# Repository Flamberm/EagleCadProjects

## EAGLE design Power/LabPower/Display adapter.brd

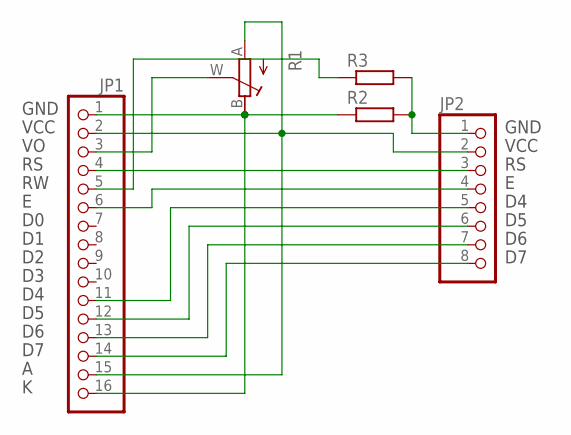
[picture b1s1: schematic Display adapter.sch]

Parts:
JP1: PINHD-1X16; 1X16
JP2: PINHD-1X8; 1X08
R1: R_POTTURN-X; RJ9W
R2, R3: R_1206; R1206

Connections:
unnamed: JP1.5, R3.1
unnamed: JP2.1, R2.2, R3.2
unnamed: JP1.11, JP2.5
unnamed: JP1.6, JP2.4
unnamed: JP1.4, JP2.3
unnamed: JP1.1, JP1.16, R1.B (E), R2.1
unnamed: JP1.2, JP1.15, JP2.2, R1.A
unnamed: JP1.3, R1.W (S)
unnamed: JP1.12, JP2.6
unnamed: JP1.13, JP2.7
unnamed: JP1.14, JP2.8

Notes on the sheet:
GND
VCC

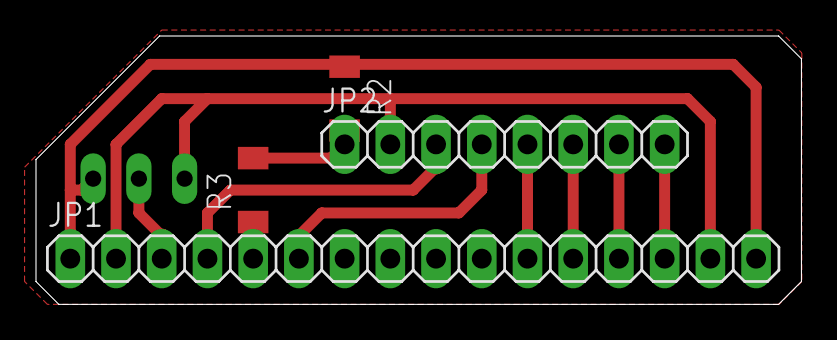
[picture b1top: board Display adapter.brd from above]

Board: 2 copper layers, 42.5 x 14.9 mm, 5 parts (1 on the bottom side), 11 nets.

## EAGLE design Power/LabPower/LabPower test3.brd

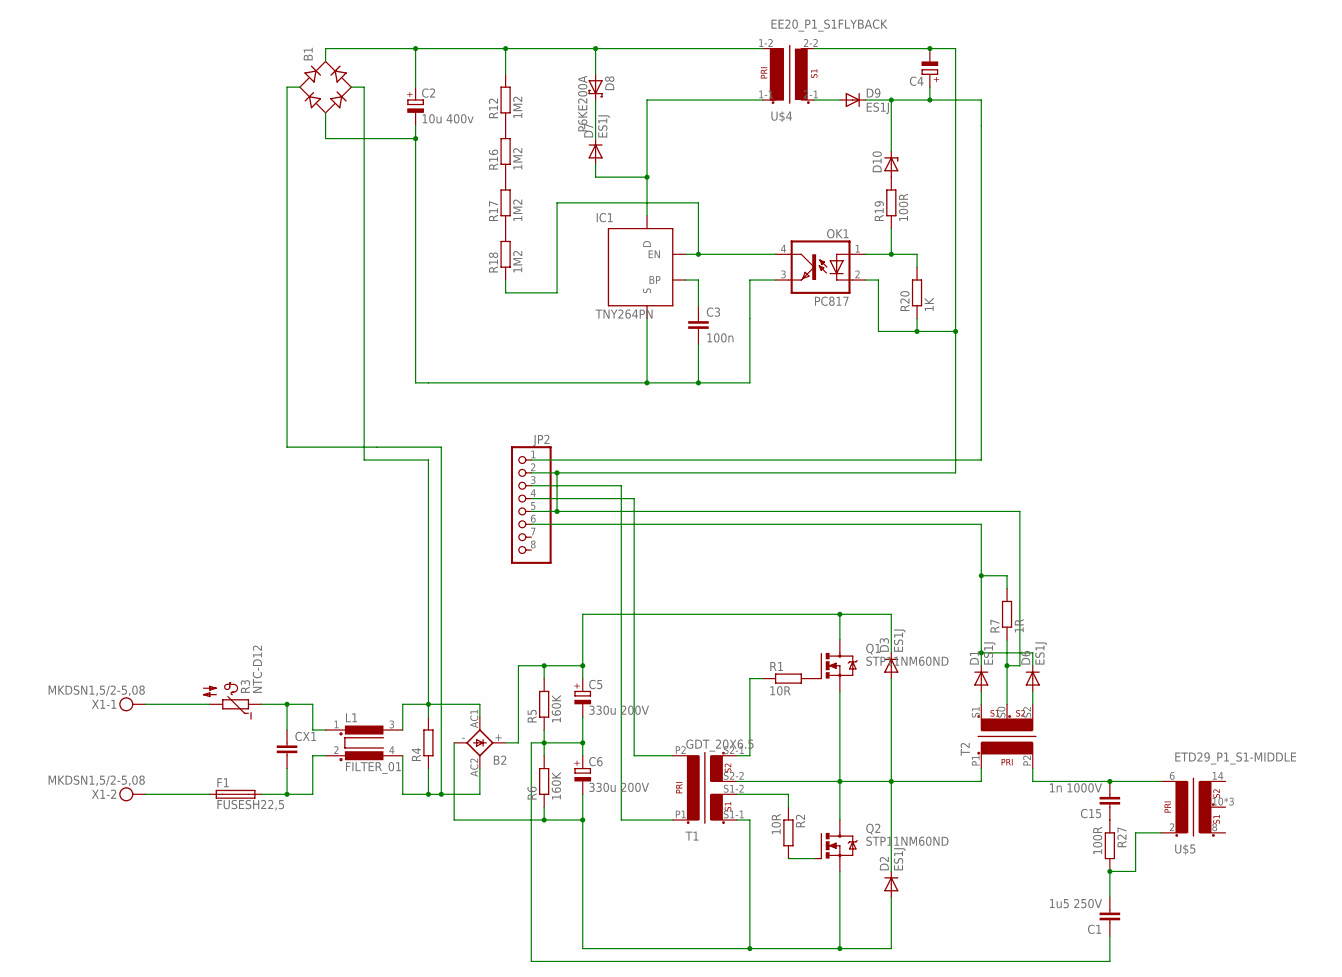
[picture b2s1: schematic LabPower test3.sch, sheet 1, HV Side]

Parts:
B1: RB1A
B2: KBL
C1: 1u5 250V; C225-074X268
C2: 10u 400v; E5-13
C3: 100n; C0805
C4: CPOL-EUE2.5-7; E2,5-7
C5, C6: 330u 200V; EB22,5D
C15: 1n 1000V; C050-025X075
CX1: CXXC15B8; XC15B8
D1, D2, D3, D6, D7, D9: ES1J; DO214AC
D8: P6KE200A; CB417-15
D10: ZENER-DIODEDO41Z10; DO41Z10
F1: FUSESH22,5; SH22,5
IC1: TNY264PN; DIP-8B
JP2: PINHD-1X8; 1X08
L1: FILTER_01; 82721K
OK1: PC817; DIL04
Q1, Q2: STP11NM60ND; TO220BV
R1, R2: 10R; R0805
R3: NTC-D12
R4: R-EU_0309/10; 0309/10
R5, R6: 160K; 0207/12
R7: 1R; R1206
R12, R16, R17, R18: 1M2; R0805
R19: 100R; R0805
R20: 1K; R0805
R27: 100R; 0617/17
T1: GDT_20X6.5
T2: CURRENT; T_10X6X3
U$4: EE20_P1_S1FLYBACK; EE20_P1_S1-REV-4PIN
U$5: ETD29_P1_S1-MIDDLE; ETD29
X1: MKDSN1,5/2-5,08

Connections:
300V: B2.+, C5.+, D3.C, Q1.D, R5.2
AC1: B1.AC1, B2.AC2 (AC1), L1.4, R4.1
AC2: B1.AC2, B2.AC1 (AC2), L1.3 (2), R4.2
unnamed: C1.1, C5.-, C6.+, R5.1, R6.2
unnamed: D2.C, D3.A, Q1.S, Q2.D, T1.S2-2, T2.P1 (P1-1)
unnamed: C1.2, R27.2, U$5.2 (P1-1)
unnamed: C15.2, T2.P2 (P1-2), U$5.6 (P1-2)
unnamed: F1.1, X1.2
unnamed: R3.2, X1.1
unnamed: CX1.1, L1.1, R3.1
unnamed: CX1.2, F1.2, L1.2 (3)
unnamed: B2.-, C6.-, D2.A, Q2.S, R6.1, T1.S1-1
unnamed: JP2.3, T1.P1 (P1-1)
unnamed: Q1.G, R1.2
unnamed: Q2.G, R2.2
unnamed: JP2.4, T1.P2 (P1-2)
unnamed: R1.1, T1.S2-1
unnamed: R2.1, T1.S1-2
unnamed: D1.A, T2.S1
unnamed: D6.A, T2.S2
unnamed: D1.C, D6.C, JP2.6, R7.2
unnamed: C4.-, JP2.2, JP2.5, OK1.2 (C), R7.1, R20.1, T2.S0 (SM), U$4.2-2 (S1-2)
unnamed: B1.+, C2.+, D8.A, R12.2, U$4.1-2
unnamed: C15.1, R27.1
unnamed: B1.-, C2.-, C3.2, IC1.2 (S), IC1.3 (S), IC1.7 (S), IC1.8 (S), OK1.3 (EMIT)
unnamed: D7.A, IC1.5 (D), U$4.1-1
unnamed: D7.C, D8.C
unnamed: C3.1, IC1.1 (BP)
unnamed: IC1.4 (EN), OK1.4 (COL), R18.1
unnamed: C4.+, D9.C, D10.C, JP2.1
unnamed: R12.1, R16.2
unnamed: R16.1, R17.2
unnamed: R17.1, R18.2
unnamed: D10.A, R19.2
unnamed: OK1.1 (A), R19.1, R20.2
unnamed: D9.A, U$4.2-1 (S1-1)

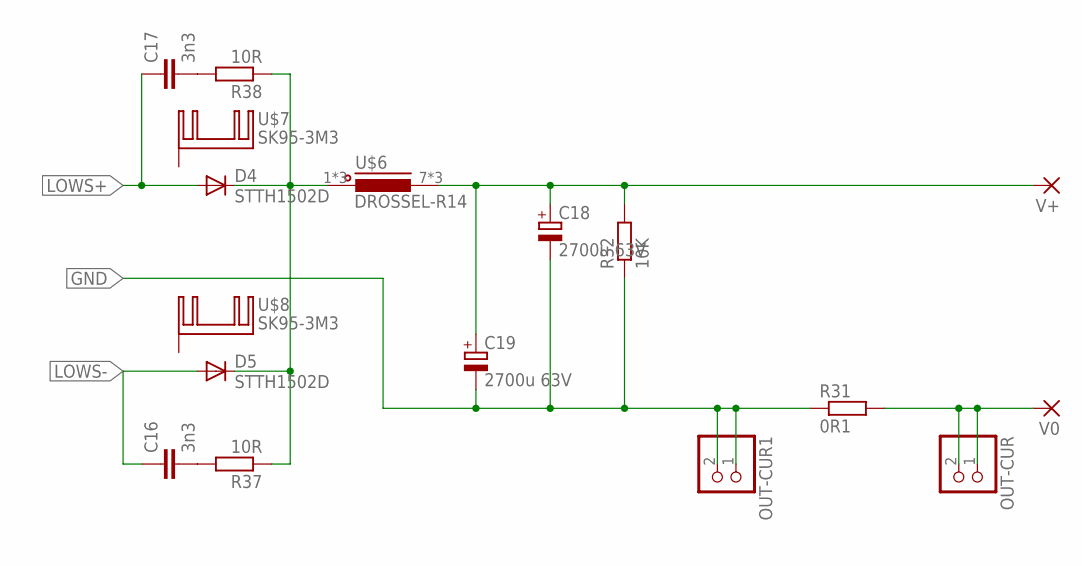
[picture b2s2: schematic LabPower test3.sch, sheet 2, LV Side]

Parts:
C16, C17: 3n3; C0805
C18, C19: 2700u 63V; E7,5-18
D4, D5: STTH1502D; DO220S
OUT-CUR, OUT-CUR1: PINHD-1X2; 1X02
R31: 0R1; SQP-10
R32: 10K; 0207/10
R37, R38: 10R; R0805
U$6: DROSSEL-R14; RM14
U$7, U$8: SK95-3M3
V0: 3,81/1,4
V+: 3,81/1,4

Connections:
GND: C18.-, C19.-, OUT-CUR1.1, OUT-CUR1.2, R31.P$1 (1), R32.1
LOWS+: C17.1, D4.A
LOWS-: C16.1, D5.A
unnamed: D4.C, D5.C, R37.1, R38.1, U$6.1, U$6.2 (1), U$6.3 (1)
unnamed: C18.+, C19.+, R32.2, U$6.7 (2), U$6.8 (2), U$6.9 (2), V+.1
unnamed: OUT-CUR.1, OUT-CUR.2, R31.P$2 (2), V0.1
unnamed: C16.2, R37.2
unnamed: C17.2, R38.2

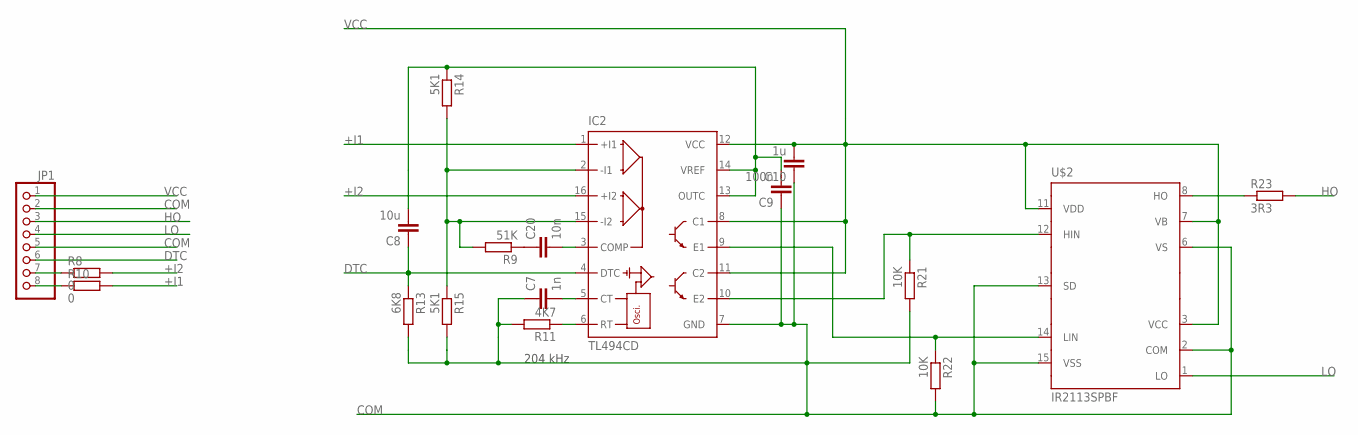
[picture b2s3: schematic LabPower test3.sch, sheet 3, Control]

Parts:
C7: 1n; C0805
C8: 10u; C0805
C9: 100n; C0805
C10: 1u; C0805
C20: 10n; C0805
IC2: TL494CD; SO16
JP1: PINHD-1X8; 1X08
R8, R10: 0; R1206
R9: 51K; R0805
R11: 4K7; R0805
R13: 6K8; R0805
R14, R15: 5K1; R0805
R21, R22: 10K; R0805
R23: 3R3; R1206
U$2: IR2113SPBF; SO16W

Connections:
+I1: IC2.1 (+I1), R10.2
+I2: IC2.16 (+I2), R8.2
COM: C7.1, C9.1, C10.1, IC2.7 (GND), JP1.2, JP1.5, R11.2, R13.2, R15.2, R21.2, R22.2, U$2.2 (COM), U$2.6 (VS), U$2.13 (SD), U$2.15 (VSS)
DTC: C8.1, IC2.4 (DTC), JP1.6, R13.1
HO: JP1.3, R23.2
LO: JP1.4, U$2.1 (LO)
unnamed: R23.1, U$2.8 (HO)
unnamed: C8.2, C9.2, IC2.13 (OUTC), IC2.14 (VREF), R14.1
unnamed: C20.1, R9.1
unnamed: C20.2, IC2.3 (COMP)
unnamed: JP1.8, R10.1
unnamed: IC2.6 (RT), R11.1
unnamed: JP1.7, R8.1
unnamed: C7.2, IC2.5 (CT)
unnamed: IC2.2 (-I1), IC2.15 (-I2), R9.2, R14.2, R15.1
unnamed: IC2.10 (E2), R21.1, U$2.12 (HIN)
unnamed: IC2.9 (E1), R22.1, U$2.14 (LIN)
VCC: C10.2, IC2.8 (C1), IC2.11 (C2), IC2.12 (VCC), JP1.1, U$2.3 (VCC), U$2.7 (VB), U$2.11 (VDD)

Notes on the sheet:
204 kHz

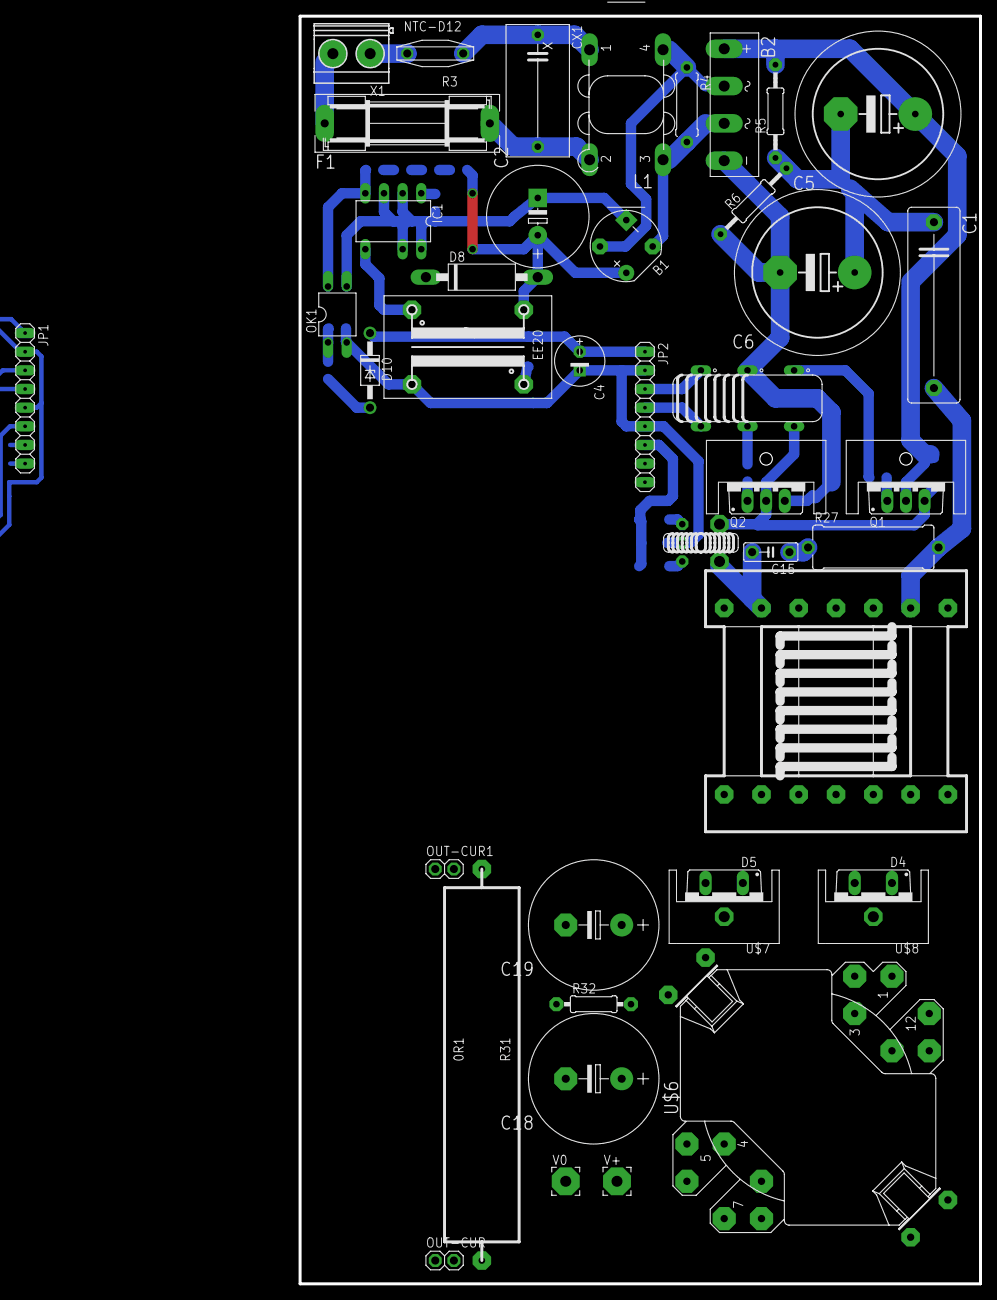
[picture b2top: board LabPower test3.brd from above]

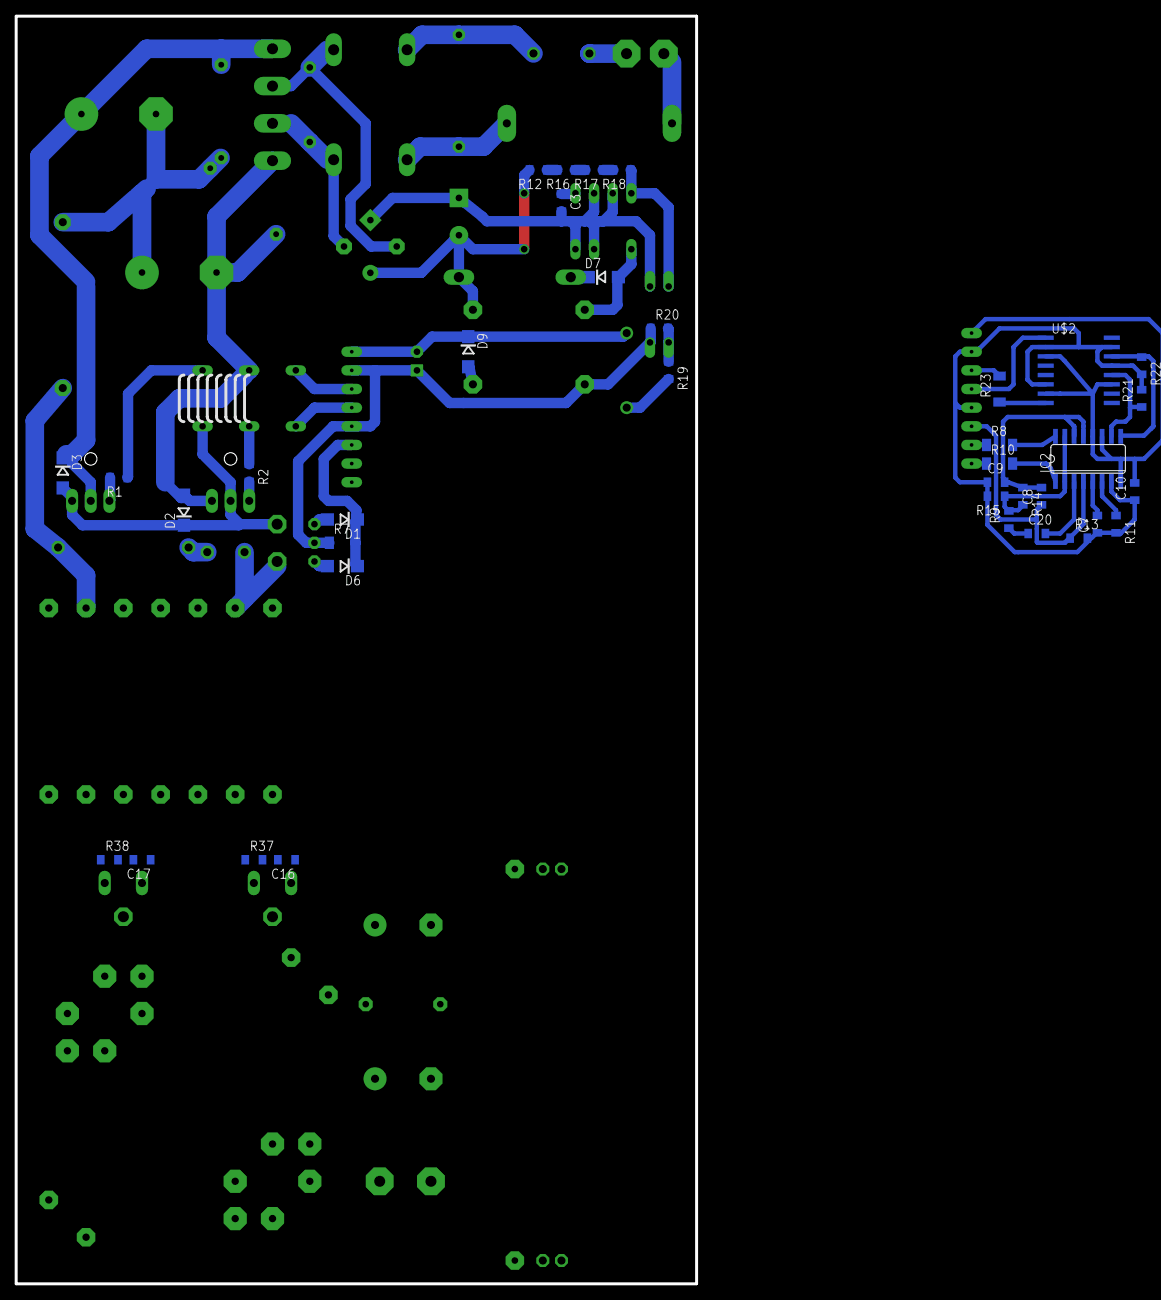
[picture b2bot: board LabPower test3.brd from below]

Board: 2 copper layers, 92.7 x 172.7 mm, 82 parts (37 on the bottom side), 62 nets.

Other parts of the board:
DRILEGEND: DRILEGEND
U$1, U$3: SK95-3M3_HOLE

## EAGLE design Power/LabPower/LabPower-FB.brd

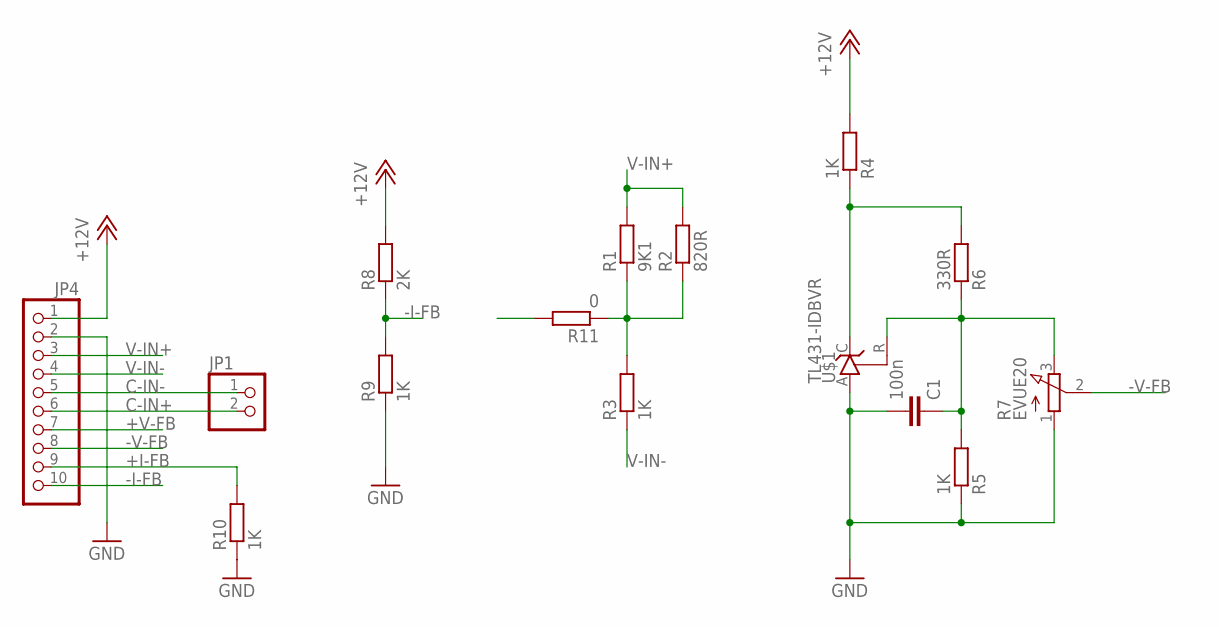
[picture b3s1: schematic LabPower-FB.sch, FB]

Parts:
C1: 100n; C0805
JP1: PINHD-1X2/90; 1X02/90
JP4: PINHD-1X10; 1X10
R1: 9K1; R0805
R2: 820R; R0805
R3, R4, R5, R9, R10: 1K; R0805
R6: 330R; R0805
R7: EVUE20; EVUE
R8: 2K; R0805
R11: 0; R0805
U$1: TL431-IDBVR; SOT23-5

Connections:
+12V: JP4.1, R4.2, R8.2
+I-FB: JP4.9, R10.2
+V-FB: JP4.7, R11.2
-I-FB: JP4.10, R8.1, R9.2
-V-FB: JP4.8, R7.2 (S)
C-IN+: JP1.2, JP4.6
C-IN-: JP1.1, JP4.5
GND: C1.2, JP4.2, R5.1, R7.1 (A), R9.1, R10.1, U$1.A
unnamed: R4.1, R6.2, U$1.C
unnamed: C1.1, R5.2, R6.1, R7.3 (E), U$1.R
unnamed: R1.1, R2.1, R3.2, R11.1
V-IN+: JP4.3, R1.2, R2.2
V-IN-: JP4.4, R3.1

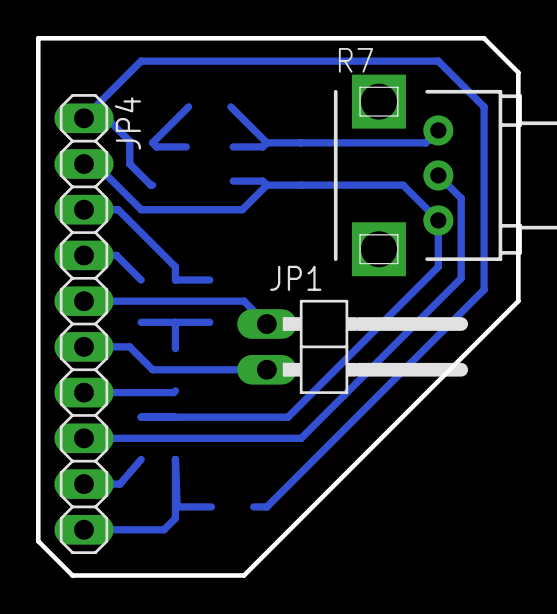
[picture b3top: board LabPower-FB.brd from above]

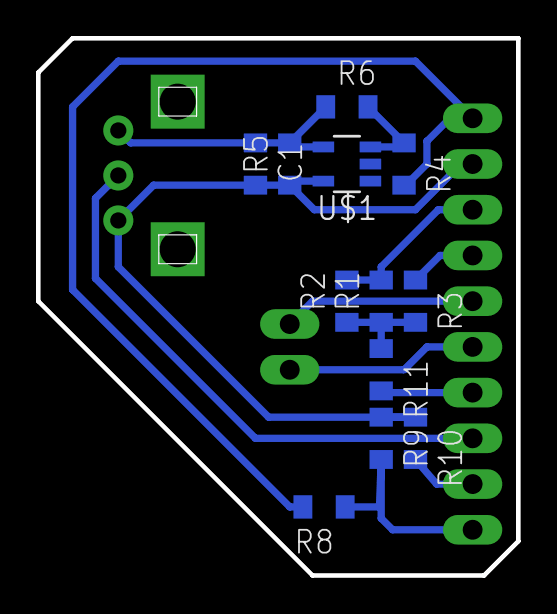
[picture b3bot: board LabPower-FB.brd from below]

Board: 2 copper layers, 26.7 x 29.8 mm, 15 parts (12 on the bottom side), 13 nets.

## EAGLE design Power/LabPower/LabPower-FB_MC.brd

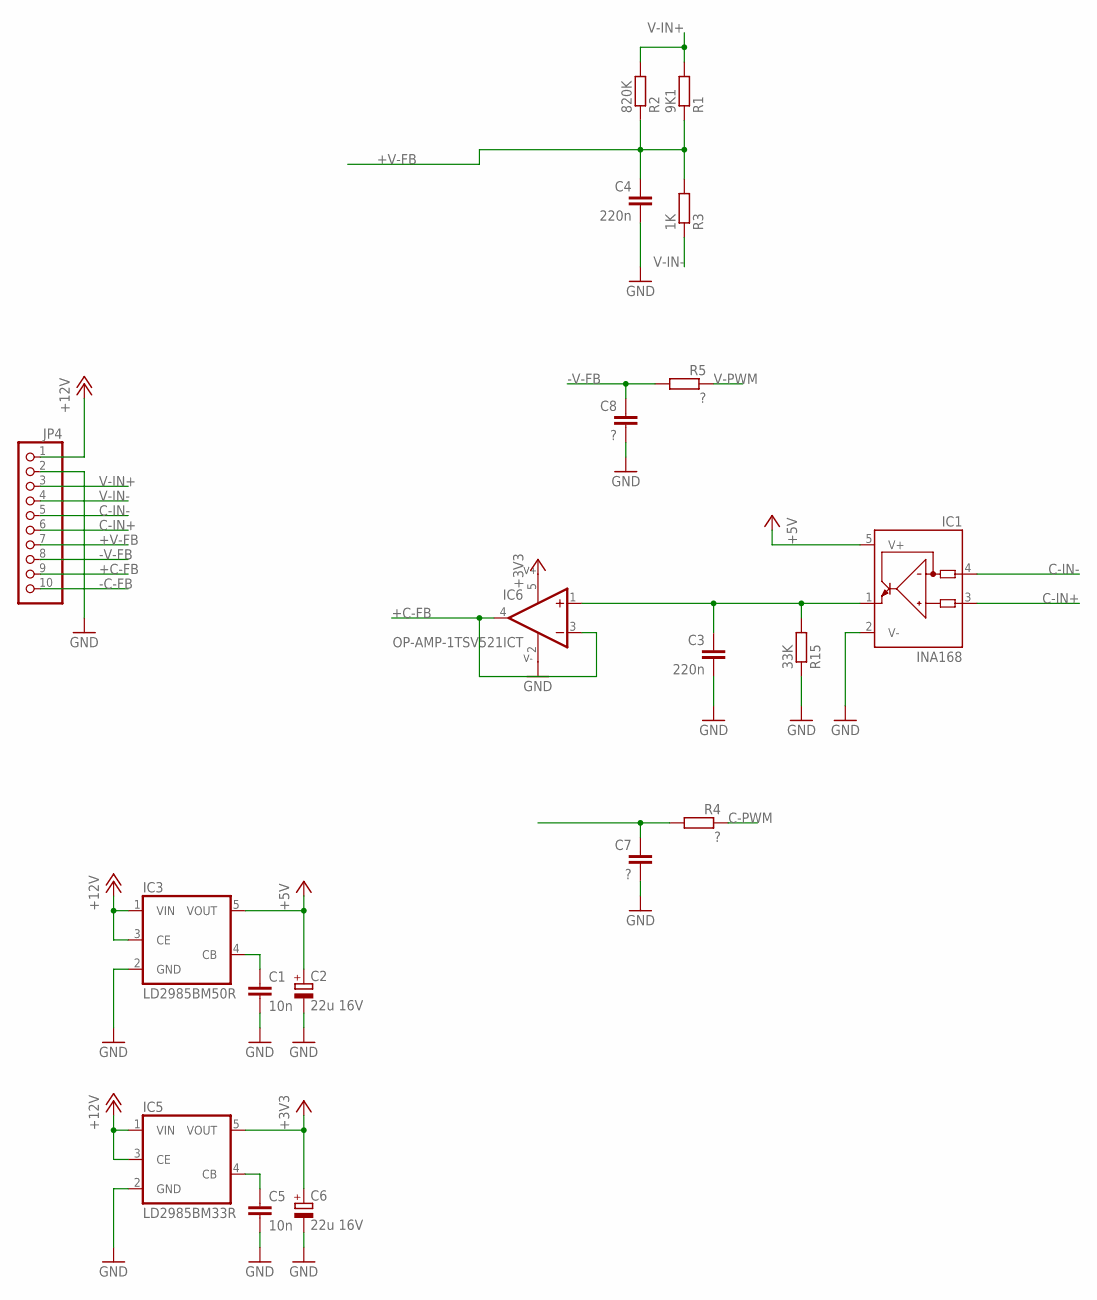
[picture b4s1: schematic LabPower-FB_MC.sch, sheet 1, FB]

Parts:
C1, C5: 10n; C0805
C2, C6: 22u 16V; B/3528-21W
C3, C4: 220n; C0805
C7, C8: ?; C0805
IC1: INA168; SOT23-5
IC3: LD2985BM50R; SOT25
IC5: LD2985BM33R; SOT25
IC6: OP-AMP-1TSV521ICT; SC70-5L
JP4: PINHD-1X10/90; 1X10/90
R1: 9K1; R0805
R2: 820K; R0805
R3: 1K; R0805
R4, R5: ?; R0805
R15: 33K; R0805

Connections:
+3V3: C6.+, IC5.5 (VOUT), IC6.5 (V+); also elsewhere on the board
+5V: C2.+, IC1.5 (V+), IC3.5 (VOUT)
+12V: IC3.1 (VIN), IC3.3 (CE), IC5.1 (VIN), IC5.3 (CE), JP4.1
+C-FB: IC6.3 (-IN), IC6.4 (OUT), JP4.9; also elsewhere on the board
+V-FB: C4.1, JP4.7, R1.1, R2.1, R3.2; also elsewhere on the board
-C-FB: C7.1, JP4.10, R4.2
-V-FB: C8.1, JP4.8, R5.2
C-IN+: IC1.3 (IN+), JP4.6
C-IN-: IC1.4 (IN-), JP4.5
C-PWM: R4.1; also elsewhere on the board
GND: C1.2, C2.-, C3.2, C4.2, C5.2, C6.-, C7.2, C8.2, IC1.2 (V-), IC3.2 (GND), IC5.2 (GND), IC6.2 (V-), JP4.2, R15.1; also elsewhere on the board
unnamed: C5.1, IC5.4 (CB)
unnamed: C3.1, IC1.1 (OUT), IC6.1 (+IN), R15.2
unnamed: C1.1, IC3.4 (CB)
V-IN+: JP4.3, R1.2, R2.2
V-IN-: JP4.4, R3.1
V-PWM: R5.1; also elsewhere on the board

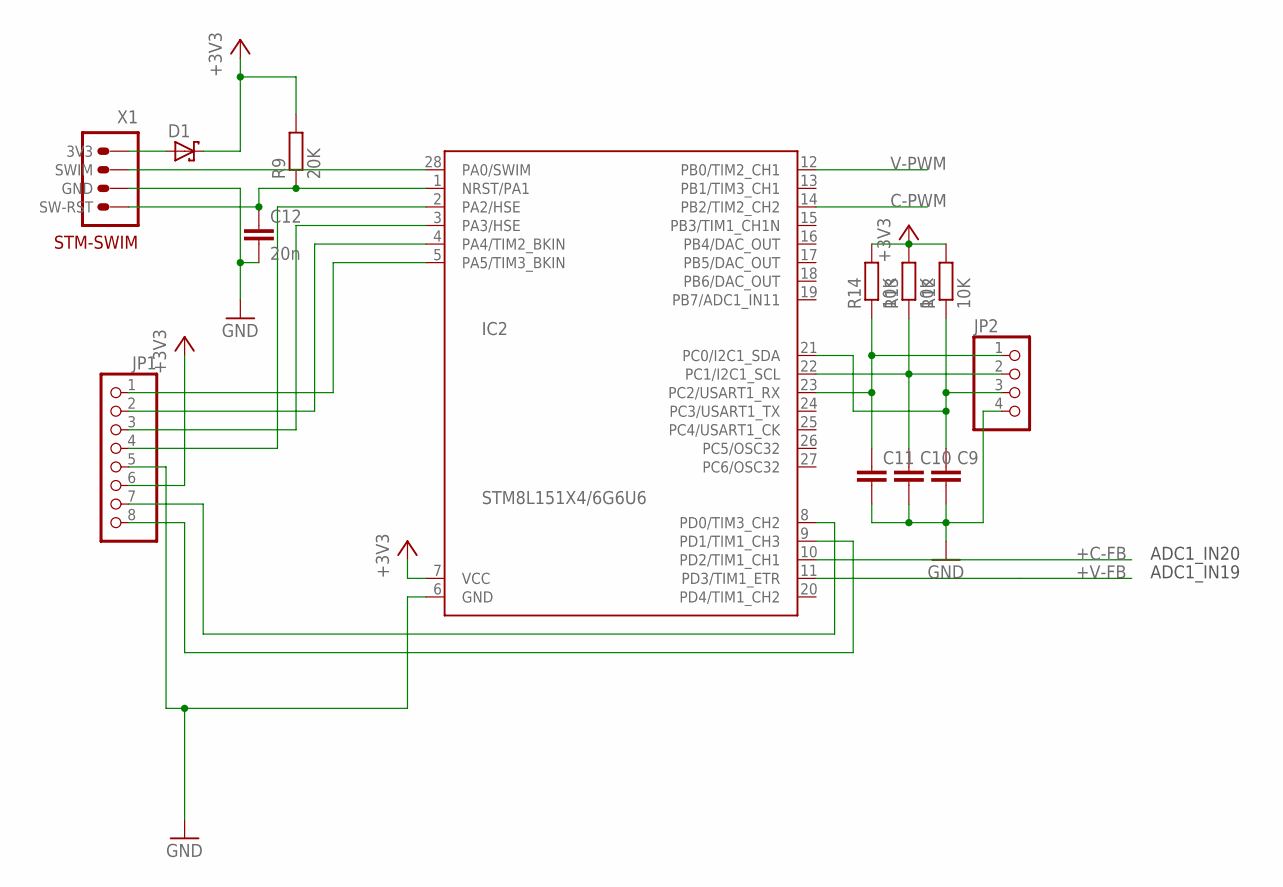
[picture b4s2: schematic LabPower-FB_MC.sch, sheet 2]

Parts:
C9, C10, C11: CAP_0805; C0805
C12: 20n; C0805
D1: DIODE-SH_SOD523; SOD523
IC2: STM8L151X4/6G6U6; QFN28
JP1: PINHD-1X8; 1X08
JP2: PINHD-1X4; 1X04
R9: 20K; R0805
R12, R13, R14: 10K; R0805
X1: STM-SWIMPINS; 1X04/90

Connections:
+3V3: D1.C, IC2.7 (VCC), JP1.6, R9.2, R12.2, R13.2, R14.2; also elsewhere on the board
+C-FB: IC2.10 (PD2/TIM1_CH1); also elsewhere on the board
+V-FB: IC2.11 (PD3/TIM1_ETR); also elsewhere on the board
C-PWM: IC2.14 (PB2/TIM2_CH2); also elsewhere on the board
GND: C9.2, C10.2, C11.2, C12.2, IC2.6 (GND), JP1.5, JP2.4, X1.3 (GND); also elsewhere on the board
unnamed: IC2.28 (PA0/SWIM), X1.2 (SWIM)
unnamed: C12.1, IC2.1 (NRST/PA1), R9.1, X1.4 (SW-RST)
unnamed: IC2.2 (PA2/HSE), JP1.4
unnamed: D1.A, X1.1 (3V3)
unnamed: IC2.3 (PA3/HSE), JP1.3
unnamed: IC2.4 (PA4/TIM2_BKIN), JP1.2
unnamed: IC2.5 (PA5/TIM3_BKIN), JP1.1
unnamed: C11.1, IC2.23 (PC2/USART1_RX), JP2.1, R14.1
unnamed: C10.1, IC2.22 (PC1/I2C1_SCL), JP2.2, R13.1
unnamed: IC2.8 (PD0/TIM3_CH2), JP1.7
unnamed: IC2.9 (PD1/TIM1_CH3), JP1.8
unnamed: C9.1, IC2.21 (PC0/I2C1_SDA), JP2.3, R12.1
V-PWM: IC2.12 (PB0/TIM2_CH1); also elsewhere on the board

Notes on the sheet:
ADC1_IN20
ADC1_IN19

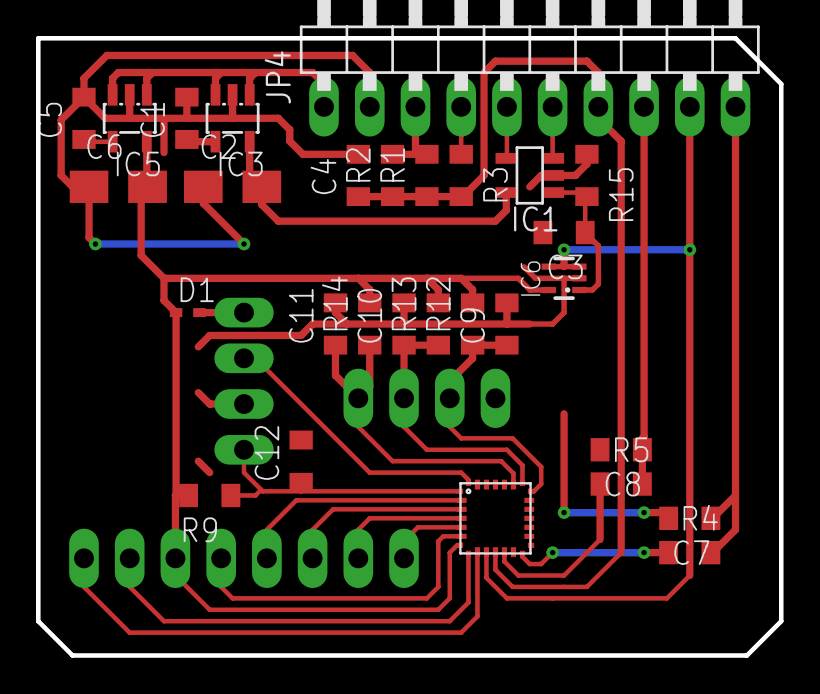
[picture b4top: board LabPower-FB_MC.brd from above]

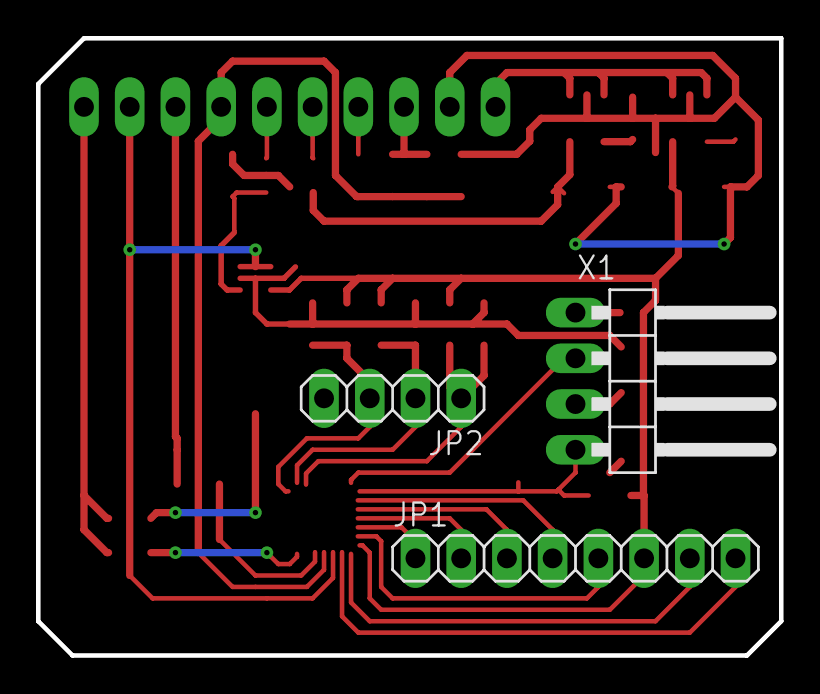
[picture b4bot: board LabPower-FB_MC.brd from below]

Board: 2 copper layers, 41.3 x 34.3 mm, 32 parts (3 on the bottom side), 29 nets.

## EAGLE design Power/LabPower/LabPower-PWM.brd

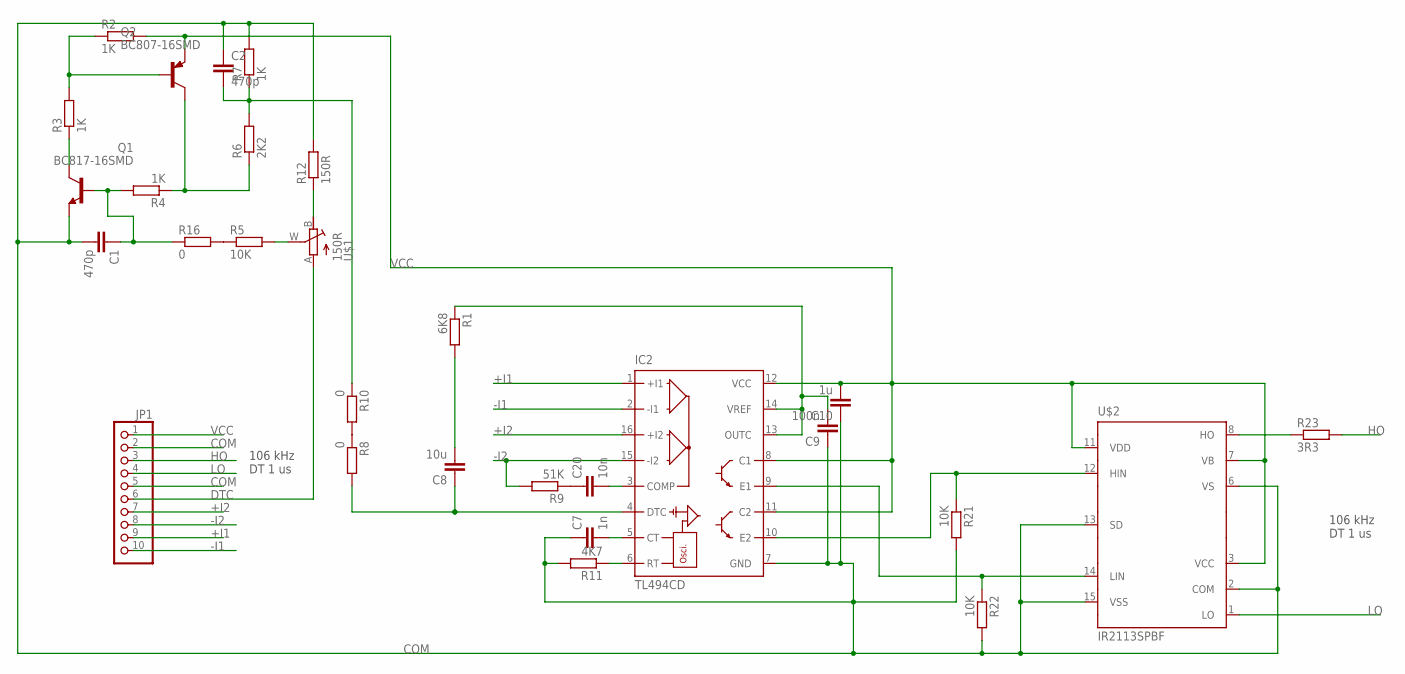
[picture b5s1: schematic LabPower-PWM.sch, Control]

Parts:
C1, C2: 470p; C0805
C7: 1n; C0805
C8: 10u; C0805
C9: 100n; C0805
C10: 1u; C0805
C20: 10n; C0805
IC2: TL494CD; SO16
JP1: PINHD-1X10; 1X10
Q1: BC817-16SMD; SOT23-BEC
Q2: BC807-16SMD; SOT23-BEC
R1: 6K8; R0805
R2, R3, R4, R7: 1K; R0805
R5, R21, R22: 10K; R0805
R6: 2K2; R0805
R8, R10, R16: 0; R0805
R9: 51K; R0805
R11: 4K7; R0805
R12: 150R; R0805
R23: 3R3; R0805
U$1: 150R; RJ9W
U$2: IR2113SPBF; SO16W

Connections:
1: C8.1, IC2.4 (DTC), R8.2
+I1: IC2.1 (+I1), JP1.9
+I2: IC2.16 (+I2), JP1.7
-I1: IC2.2 (-I1), JP1.10
-I2: IC2.15 (-I2), JP1.8, R9.2
COM: C1.2, C2.1, C7.1, C9.1, C10.1, IC2.7 (GND), JP1.2, JP1.5, Q1.E, R7.2, R11.2, R12.2, R21.2, R22.2, U$2.2 (COM), U$2.6 (VS), U$2.13 (SD), U$2.15 (VSS)
DTC: JP1.6, U$1.A
HO: JP1.3, R23.2
LO: JP1.4, U$2.1 (LO)
unnamed: C8.2, R1.2
unnamed: R5.2, U$1.W (S)
unnamed: Q2.B, R2.1, R3.2
unnamed: R23.1, U$2.8 (HO)
unnamed: Q1.C, R3.1
unnamed: C1.1, Q1.B, R4.2, R16.1
unnamed: Q2.C, R4.1, R6.1
unnamed: C9.2, IC2.13 (OUTC), IC2.14 (VREF), R1.1
unnamed: R12.1, U$1.B (E)
unnamed: R5.1, R16.2
unnamed: C20.1, R9.1
unnamed: C20.2, IC2.3 (COMP)
unnamed: C2.2, R6.2, R7.1, R10.1
unnamed: IC2.6 (RT), R11.1
unnamed: R8.1, R10.2
unnamed: C7.2, IC2.5 (CT)
unnamed: IC2.10 (E2), R21.1, U$2.12 (HIN)
unnamed: IC2.9 (E1), R22.1, U$2.14 (LIN)
VCC: C10.2, IC2.8 (C1), IC2.11 (C2), IC2.12 (VCC), JP1.1, Q2.E, R2.2, U$2.3 (VCC), U$2.7 (VB), U$2.11 (VDD)

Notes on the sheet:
106 kHz DT 1 us

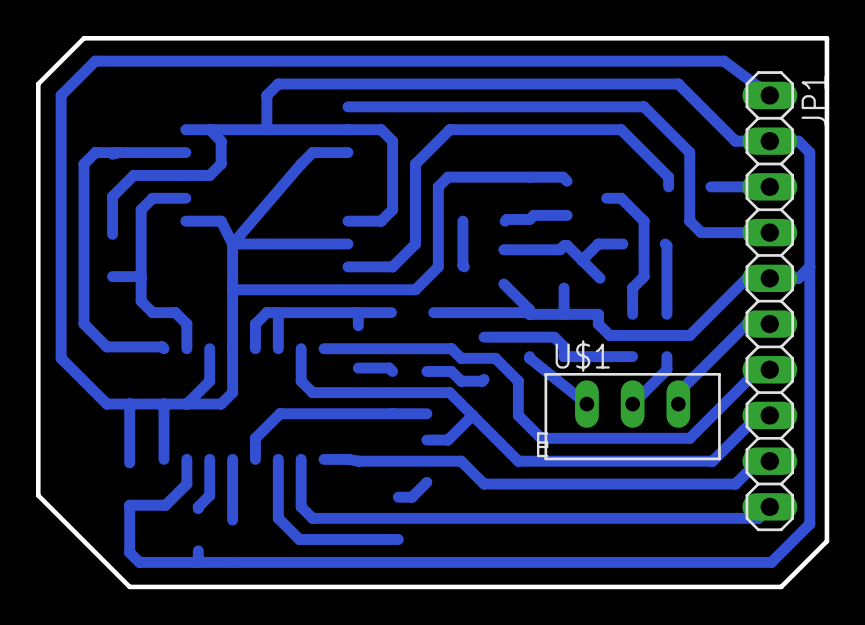
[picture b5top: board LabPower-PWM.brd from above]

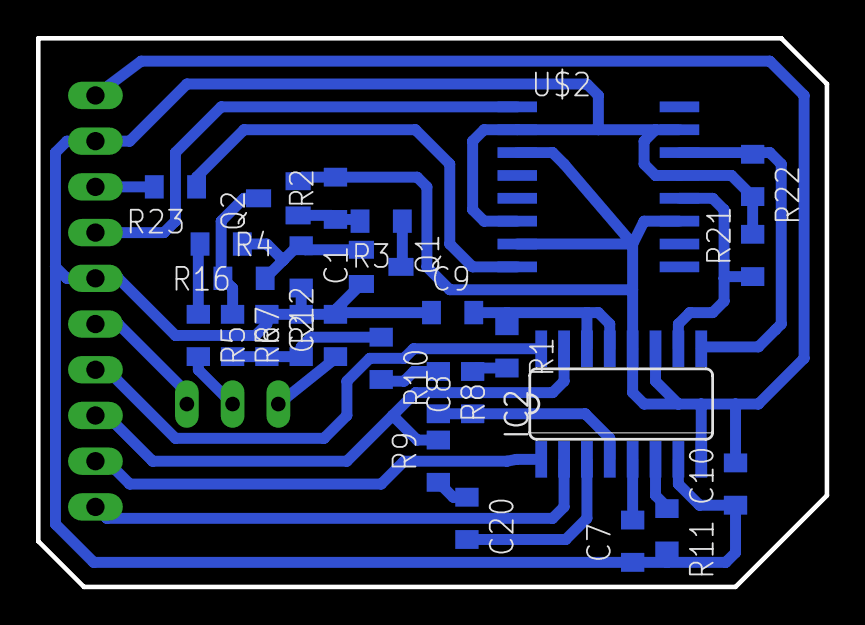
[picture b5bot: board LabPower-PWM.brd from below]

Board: 2 copper layers, 43.8 x 30.5 mm, 29 parts (27 on the bottom side), 28 nets.

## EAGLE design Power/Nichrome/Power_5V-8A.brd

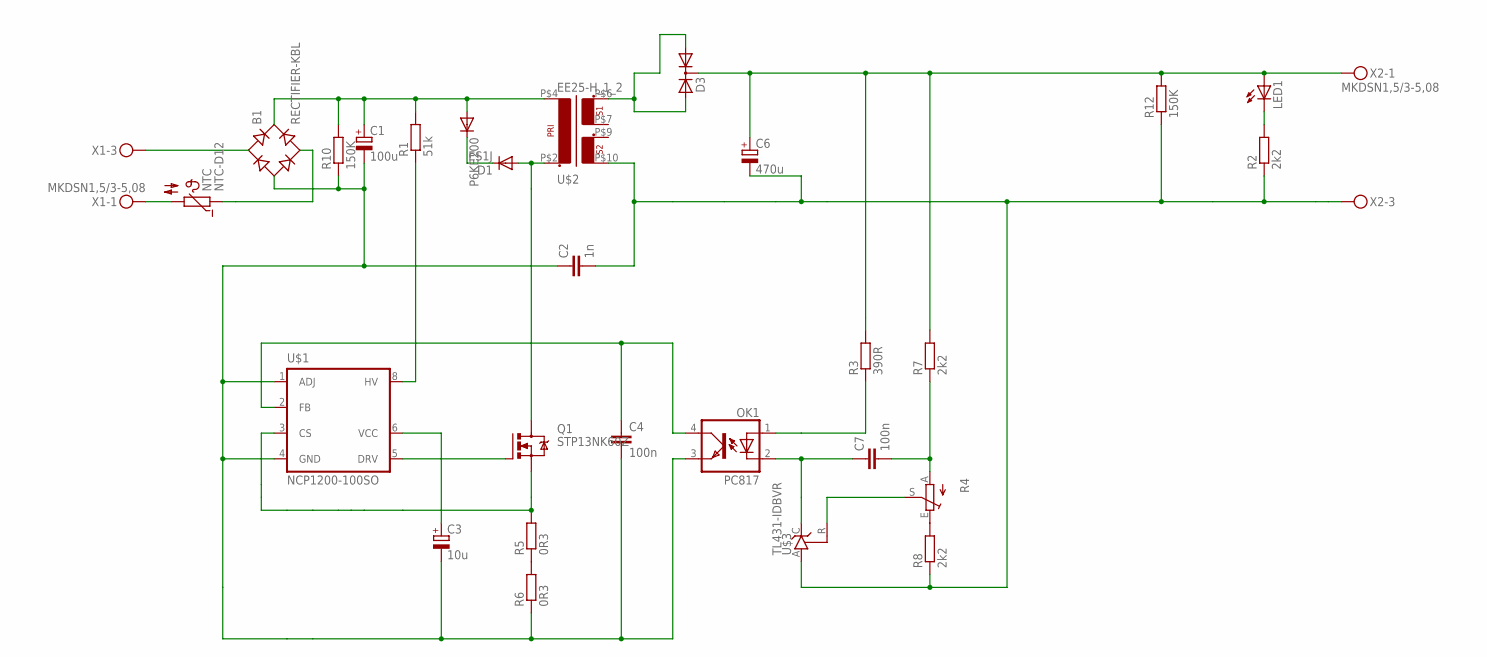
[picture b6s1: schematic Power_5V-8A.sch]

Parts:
B1: RECTIFIER-KBL; KBL
C1: 100u; EB22,5D
C2: 1n; C050-024X044
C3: 10u; E5-5
C4, C7: 100n; C0805
C6: 470u; E5-10,5
D1: ES1J; DO41-7.6
D3: DIODE-2AC|CATO220V; TO220ABS
LED1: LED5MM
NTC: NTC-D12
OK1: PC817; DIL04
P6KE200: DIODE-DO15-12; DO15-12
Q1: STP13NK60Z; TO220BV
R1: 51k; SQP-5
R2, R7, R8: 2k2; R1206
R3: 390R; R1206
R4: TRIM_EU-S75H; S75H
R5, R6: 0R3; 0411/12
R10: 150K; 0207/10
R12: 150K; R1206
U$1: NCP1200-100SO; SOP8
U$2: EE25-H_1_2; EE25
U$3: TL431-IDBVR; SOT23-5
X1, X2: MKDSN1,5/3-5,08

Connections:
unnamed: NTC.2, X1.1
unnamed: B1.AC1, X1.3
unnamed: B1.AC2, NTC.1
unnamed: R5.1, R6.2
unnamed: B1.-, C1.-, C2.1, C3.-, C4.2, OK1.3 (EMIT), R6.1, R10.1, U$1.1 (ADJ), U$1.4 (GND)
unnamed: B1.+, C1.+, P6KE200.A, R1.2, R10.2, U$2.P$4 (2)
unnamed: D1.C, P6KE200.C
unnamed: D1.A, Q1.D, U$2.P$2 (1)
unnamed: C2.2, C6.-, R2.1, R8.1, R12.1, U$2.P$10 (6), U$3.A, X2.3
unnamed: R1.1, U$1.8 (HV)
unnamed: Q1.G, U$1.5 (DRV)
unnamed: Q1.S, R5.2, U$1.3 (CS)
unnamed: LED1.K (C), R2.2
unnamed: C3.+, U$1.6 (VCC)
unnamed: C4.1, OK1.4 (COL), U$1.2 (FB)
unnamed: D3.A1, D3.A2, U$2.P$6 (3)
unnamed: C6.+, D3.C, LED1.A, R3.2, R7.2, R12.2, X2.1
unnamed: R4.S, U$3.R
unnamed: OK1.1 (A), R3.1
unnamed: C7.1, OK1.2 (C), U$3.C
unnamed: C7.2, R4.A, R7.1
unnamed: R4.E, R8.2

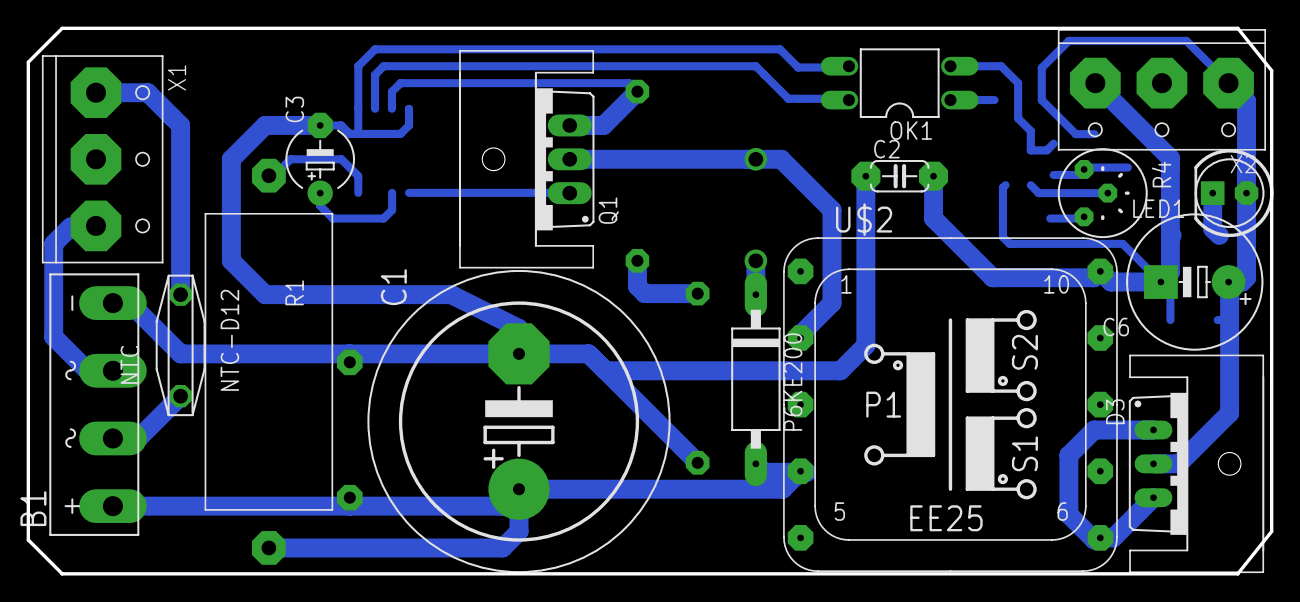
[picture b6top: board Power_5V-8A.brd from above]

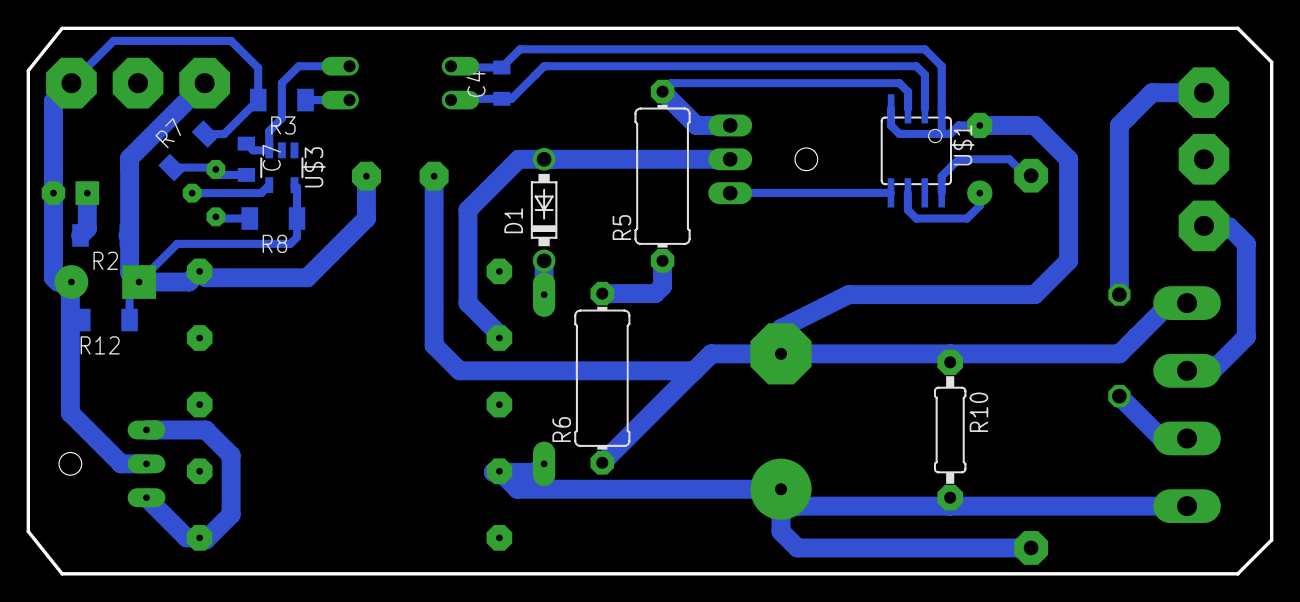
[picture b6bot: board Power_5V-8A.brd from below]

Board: 2 copper layers, 93.3 x 40.9 mm, 31 parts (13 on the bottom side), 22 nets.

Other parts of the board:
U$4, U$5: SK95-3M3_HOLE
